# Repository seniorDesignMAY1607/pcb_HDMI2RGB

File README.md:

# pcb_HDMI2RGB
KiCad Design files for HDMI to 24Bit RGB converter used to drive DLP3010 TI EVM board.

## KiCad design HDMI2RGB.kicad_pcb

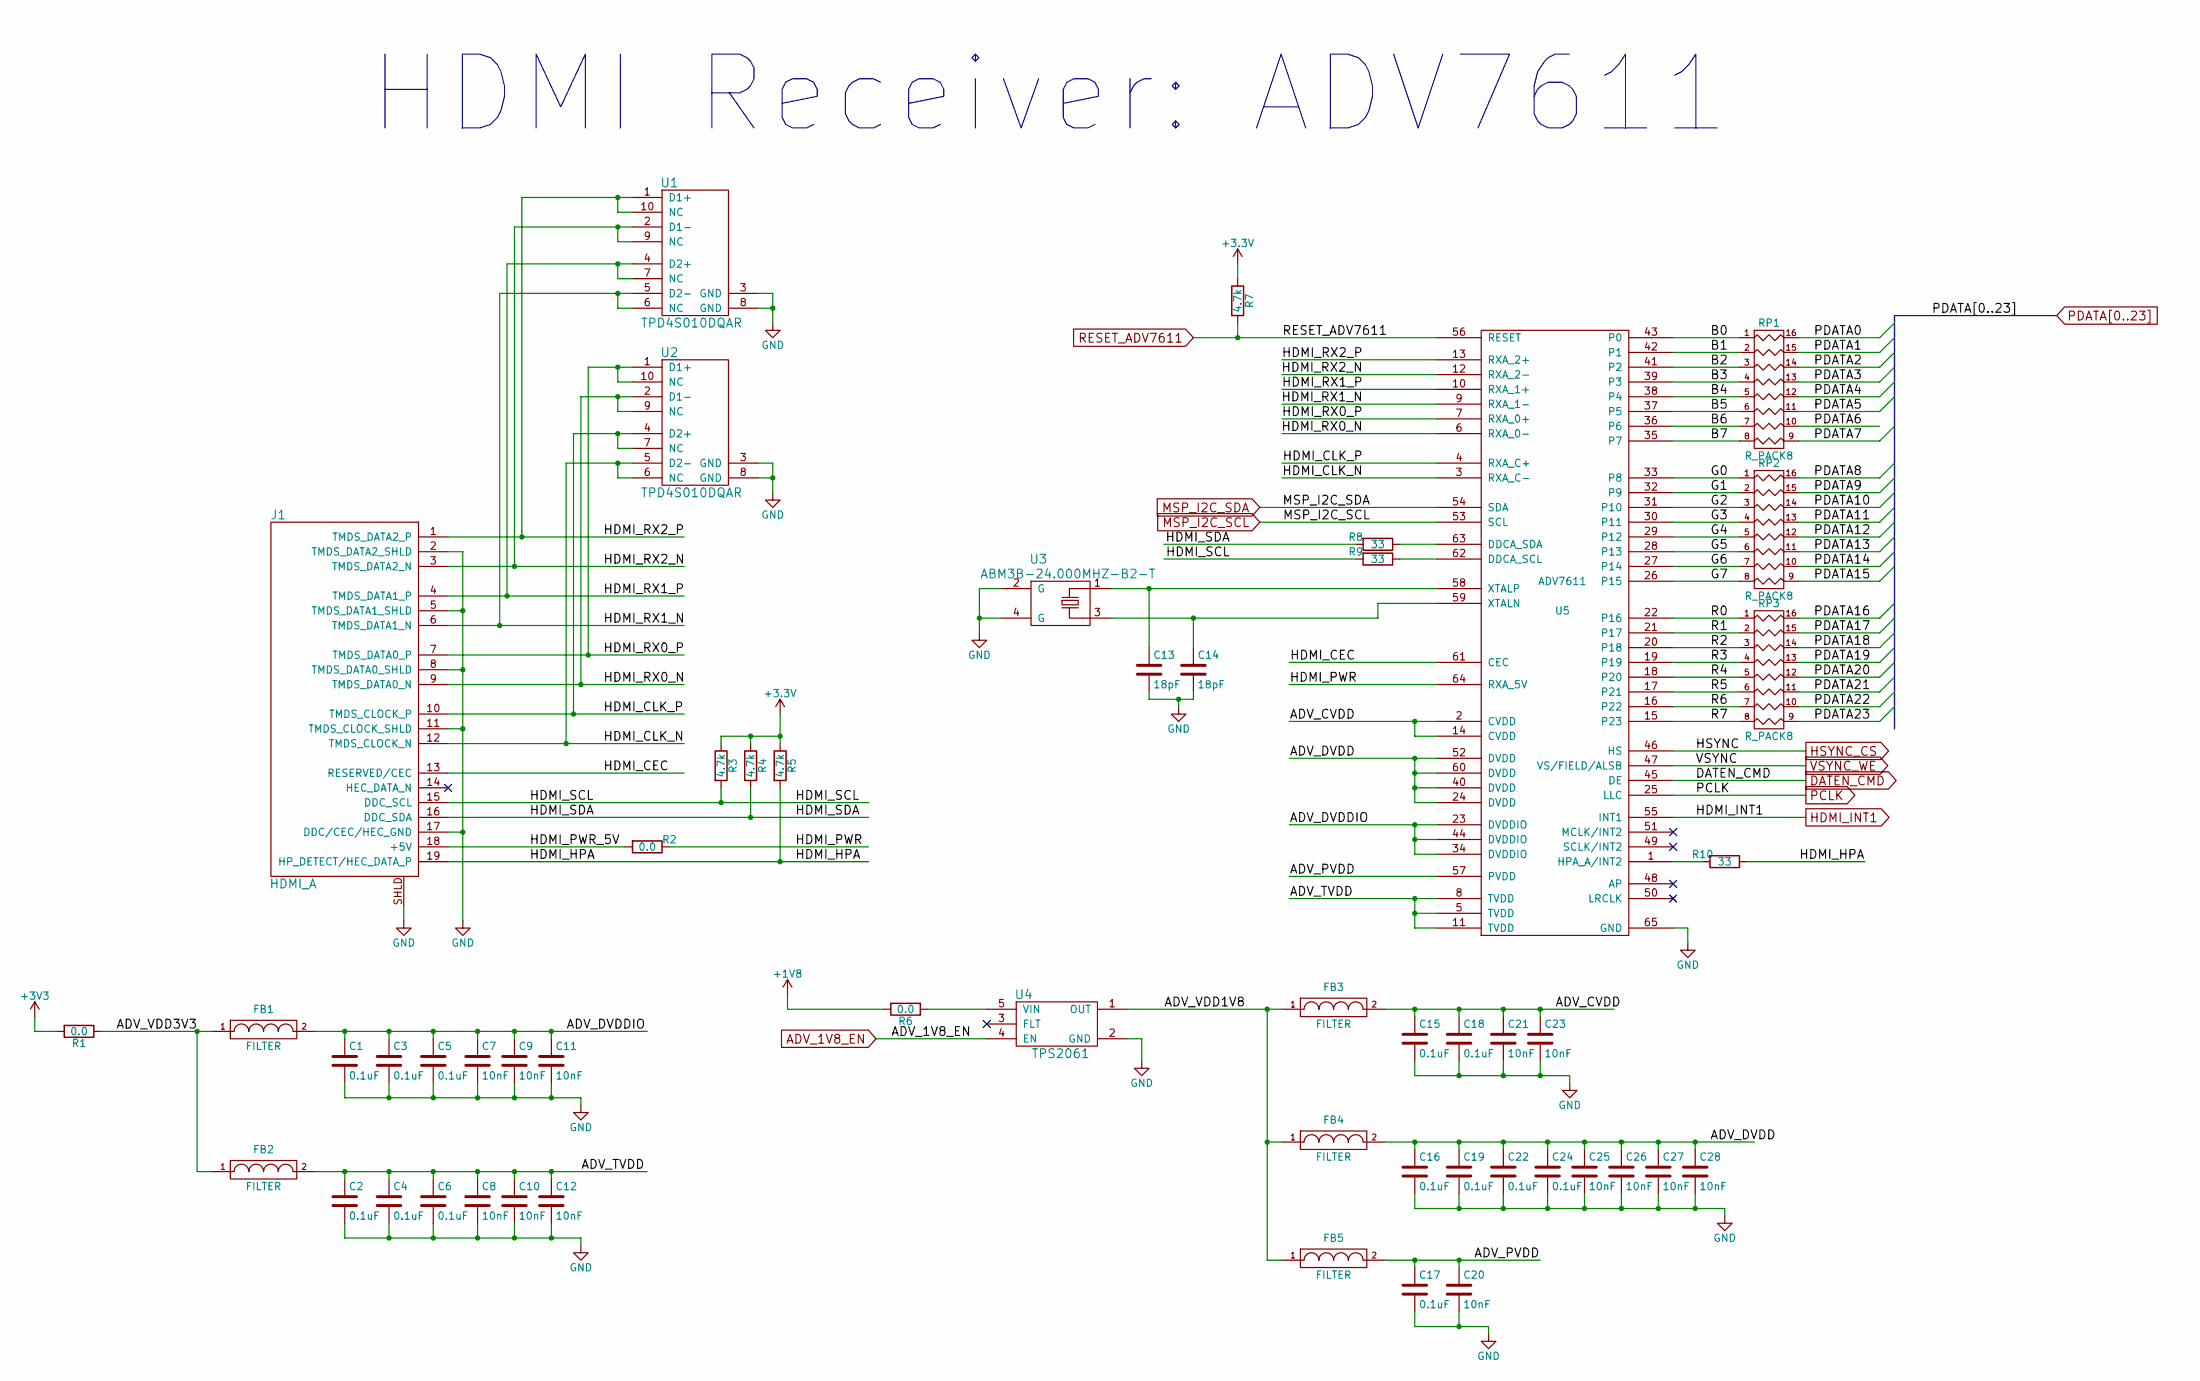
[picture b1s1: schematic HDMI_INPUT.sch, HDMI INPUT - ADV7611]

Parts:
C1, C2, C3, C4, C5, C6, C15, C16, C17, C18, C19, C22, C24: 0.1uF; C_0402; Part # 0402YD104KAT2A
C7, C8, C9, C10, C11, C12, C20, C21, C23, C25, C26, C27, C28: 10nF; C_0402; Part # C0402C103K5RACTU
C13, C14: 18pF; C_0603; Part # 06035A180JAT2A
FB1, FB2, FB3, FB4, FB5: FILTER; C_0603; Part # BLM18AG601SN1D
J1: HDMI_A; FCI_10029449-11[13]RLF
R1, R2, R6: 0.0; R_0402; Part # CRCW06030000Z0EA
R3, R4, R5, R7: 4.7k; R_0402; Part # ERJ-2GEJ472X
R8, R9: 33; R_0402; Part # CRCW040233R0FKED
R10: 33; C_0402; Part # CRCW040233R0FKED
RP1, RP2, RP3: R_PACK8; RPACK-8_0616
U1, U2: TPD4S010DQAR; 10-USON
U3: ABM3B-24.000MHZ-B2-T; XTAL_ABRACON; Part # ABM3B-24.000MHZ-B2-T
U4: TPS2061; SOT-23-5; Part # TPS2061CDBVT
U5: ADV7611; LQFP-64_TH_10x10mm_Pitch0.5mm

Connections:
+1V8: R6.2; also elsewhere on the board
/CONNECTOR/PDATA0: RP1.16 (R1); also elsewhere on the board
/CONNECTOR/PDATA1: RP1.15 (R2); also elsewhere on the board
/CONNECTOR/PDATA2: RP1.14 (R3); also elsewhere on the board
/CONNECTOR/PDATA3: RP1.13 (R4); also elsewhere on the board
/CONNECTOR/PDATA4: RP1.12 (R5); also elsewhere on the board
/CONNECTOR/PDATA5: RP1.11 (R6); also elsewhere on the board
/CONNECTOR/PDATA6: RP1.10 (R7); also elsewhere on the board
/CONNECTOR/PDATA7: RP1.9 (R8); also elsewhere on the board
/CONNECTOR/PDATA8: RP2.16 (R1); also elsewhere on the board
/CONNECTOR/PDATA9: RP2.15 (R2); also elsewhere on the board
/CONNECTOR/PDATA10: RP2.14 (R3); also elsewhere on the board
/CONNECTOR/PDATA11: RP2.13 (R4); also elsewhere on the board
/CONNECTOR/PDATA12: RP2.12 (R5); also elsewhere on the board
/CONNECTOR/PDATA13: RP2.11 (R6); also elsewhere on the board
/CONNECTOR/PDATA14: RP2.10 (R7); also elsewhere on the board
/CONNECTOR/PDATA15: RP2.9 (R8); also elsewhere on the board
/CONNECTOR/PDATA16: RP3.16 (R1); also elsewhere on the board
/CONNECTOR/PDATA17: RP3.15 (R2); also elsewhere on the board
/CONNECTOR/PDATA18: RP3.14 (R3); also elsewhere on the board
/CONNECTOR/PDATA19: RP3.13 (R4); also elsewhere on the board
/CONNECTOR/PDATA20: RP3.12 (R5); also elsewhere on the board
/CONNECTOR/PDATA21: RP3.11 (R6); also elsewhere on the board
/CONNECTOR/PDATA22: RP3.10 (R7); also elsewhere on the board
/CONNECTOR/PDATA23: RP3.9 (R8); also elsewhere on the board
/HDMI_INPUT/ADV_CVDD: C15.1, C18.1, C21.1, C23.1, FB3.2, U5.2 (CVDD), U5.14 (CVDD)
/HDMI_INPUT/ADV_DVDD: C16.1, C19.1, C22.1, C24.1, C25.1, C26.1, C27.1, C28.1, FB4.2, U5.24 (DVDD), U5.40 (DVDD), U5.52 (DVDD), U5.60 (DVDD)
/HDMI_INPUT/ADV_DVDDIO: C1.1, C3.1, C5.1, C7.1, C9.1, C11.1, FB1.2, U5.23 (DVDDIO), U5.34 (DVDDIO), U5.44 (DVDDIO)
/HDMI_INPUT/ADV_PVDD: C17.1, C20.1, FB5.2, U5.57 (PVDD)
/HDMI_INPUT/ADV_TVDD: C2.1, C4.1, C6.1, C8.1, C10.1, C12.1, FB2.2, U5.5 (TVDD), U5.8 (TVDD), U5.11 (TVDD)
/HDMI_INPUT/ADV_VDD1V8: FB3.1, FB4.1, FB5.1, U4.1 (OUT)
/HDMI_INPUT/ADV_VDD3V3: FB1.1, FB2.1, R1.1
/HDMI_INPUT/B0: RP1.1, U5.43 (P0)
/HDMI_INPUT/B1: RP1.2, U5.42 (P1)
/HDMI_INPUT/B2: RP1.3, U5.41 (P2)
/HDMI_INPUT/B3: RP1.4, U5.39 (P3)
/HDMI_INPUT/B4: RP1.5, U5.38 (P4)
/HDMI_INPUT/B5: RP1.6, U5.37 (P5)
/HDMI_INPUT/B6: RP1.7, U5.36 (P6)
/HDMI_INPUT/B7: RP1.8, U5.35 (P7)
/HDMI_INPUT/G0: RP2.1, U5.33 (P8)
/HDMI_INPUT/G1: RP2.2, U5.32 (P9)
/HDMI_INPUT/G2: RP2.3, U5.31 (P10)
/HDMI_INPUT/G3: RP2.4, U5.30 (P11)
/HDMI_INPUT/G4: RP2.5, U5.29 (P12)
/HDMI_INPUT/G5: RP2.6, U5.28 (P13)
/HDMI_INPUT/G6: RP2.7, U5.27 (P14)
/HDMI_INPUT/G7: RP2.8, U5.26 (P15)
/HDMI_INPUT/HDMI_CEC: J1.13 (RESERVED/CEC), U5.61 (CEC)
/HDMI_INPUT/HDMI_CLK_N: J1.12 (TMDS_CLOCK_N), U2.5 (D2-), U2.6 (NC), U5.3 (RXA_C-)
/HDMI_INPUT/HDMI_CLK_P: J1.10 (TMDS_CLOCK_P), U2.4 (D2+), U2.7 (NC), U5.4 (RXA_C+)
/HDMI_INPUT/HDMI_HPA: J1.19 (HP_DETECT/HEC_DATA_P), R5.2, R10.1
/HDMI_INPUT/HDMI_PWR: R2.1, U5.64 (RXA_5V)
/HDMI_INPUT/HDMI_PWR_5V: J1.18 (+5V), R2.2
/HDMI_INPUT/HDMI_RX0_N: J1.9 (TMDS_DATA0_N), U2.2 (D1-), U2.9 (NC), U5.6 (RXA_0-)
/HDMI_INPUT/HDMI_RX0_P: J1.7 (TMDS_DATA0_P), U2.1 (D1+), U2.10 (NC), U5.7 (RXA_0+)
/HDMI_INPUT/HDMI_RX1_N: J1.6 (TMDS_DATA1_N), U1.5 (D2-), U1.6 (NC), U5.9 (RXA_1-)
/HDMI_INPUT/HDMI_RX1_P: J1.4 (TMDS_DATA1_P), U1.4 (D2+), U1.7 (NC), U5.10 (RXA_1+)
/HDMI_INPUT/HDMI_RX2_N: J1.3 (TMDS_DATA2_N), U1.2 (D1-), U1.9 (NC), U5.12 (RXA_2-)
/HDMI_INPUT/HDMI_RX2_P: J1.1 (TMDS_DATA2_P), U1.1 (D1+), U1.10 (NC), U5.13 (RXA_2+)
/HDMI_INPUT/HDMI_SCL: J1.15 (DDC_SCL), R3.2, R9.2
/HDMI_INPUT/HDMI_SDA: J1.16 (DDC_SDA), R4.2, R8.2
/HDMI_INPUT/R0: RP3.1, U5.22 (P16)
/HDMI_INPUT/R1: RP3.2, U5.21 (P17)
/HDMI_INPUT/R2: RP3.3, U5.20 (P18)
/HDMI_INPUT/R3: RP3.4, U5.19
/HDMI_INPUT/R4: RP3.5, U5.18 (P20)
/HDMI_INPUT/R5: RP3.6, U5.17 (P21)
/HDMI_INPUT/R6: RP3.7, U5.16 (P22)
/HDMI_INPUT/R7: RP3.8, U5.15 (P23)
ADV_1V8_EN: U4.4 (EN); also elsewhere on the board
DATEN_CMD: U5.45 (DE); also elsewhere on the board
GND: C1.2, C2.2, C3.2, C4.2, C5.2, C6.2, C7.2, C8.2, C9.2, C10.2, C11.2, C12.2, C13.2, C14.2, C15.2, C16.2, C17.2, C18.2, C19.2, C20.2, C21.2, C22.2, C23.2, C24.2, C25.2, C26.2, C27.2, C28.2, J1.2 (TMDS_DATA2_SHLD), J1.5 (TMDS_DATA1_SHLD), J1.8 (TMDS_DATA0_SHLD), J1.11 (TMDS_CLOCK_SHLD), J1.17 (DDC/CEC/HEC_GND), J1.SHLD, U1.3 (GND), U1.8 (GND), U2.3 (GND), U2.8 (GND), U3.2 (G), U3.4 (G), U4.2 (GND), U5.65 (GND); also elsewhere on the board
HDMI_INT1: U5.55 (INT1); also elsewhere on the board
HSYNC_CS: U5.46 (HS); also elsewhere on the board
MSP_I2C_SCL: U5.53 (SCL); also elsewhere on the board
MSP_I2C_SDA: U5.54 (SDA); also elsewhere on the board
unnamed: C13.1, U3.1, U5.58 (XTALP)
unnamed: C14.1, U3.3, U5.59 (XTALN)
unnamed: R6.1, U4.5 (VIN)
unnamed: R8.1, U5.63 (DDCA_SDA)
unnamed: R9.1, U5.62 (DDCA_SCL)
unnamed: R10.2, U5.1 (HPA_A/INT2)
PCLK: U5.25 (LLC); also elsewhere on the board
RESET_ADV7611: R7.2, U5.56 (RESET); also elsewhere on the board
VSYNC_WE: U5.47 (VS/FIELD/ALSB); also elsewhere on the board

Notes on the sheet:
HDMI Receiver: ADV7611

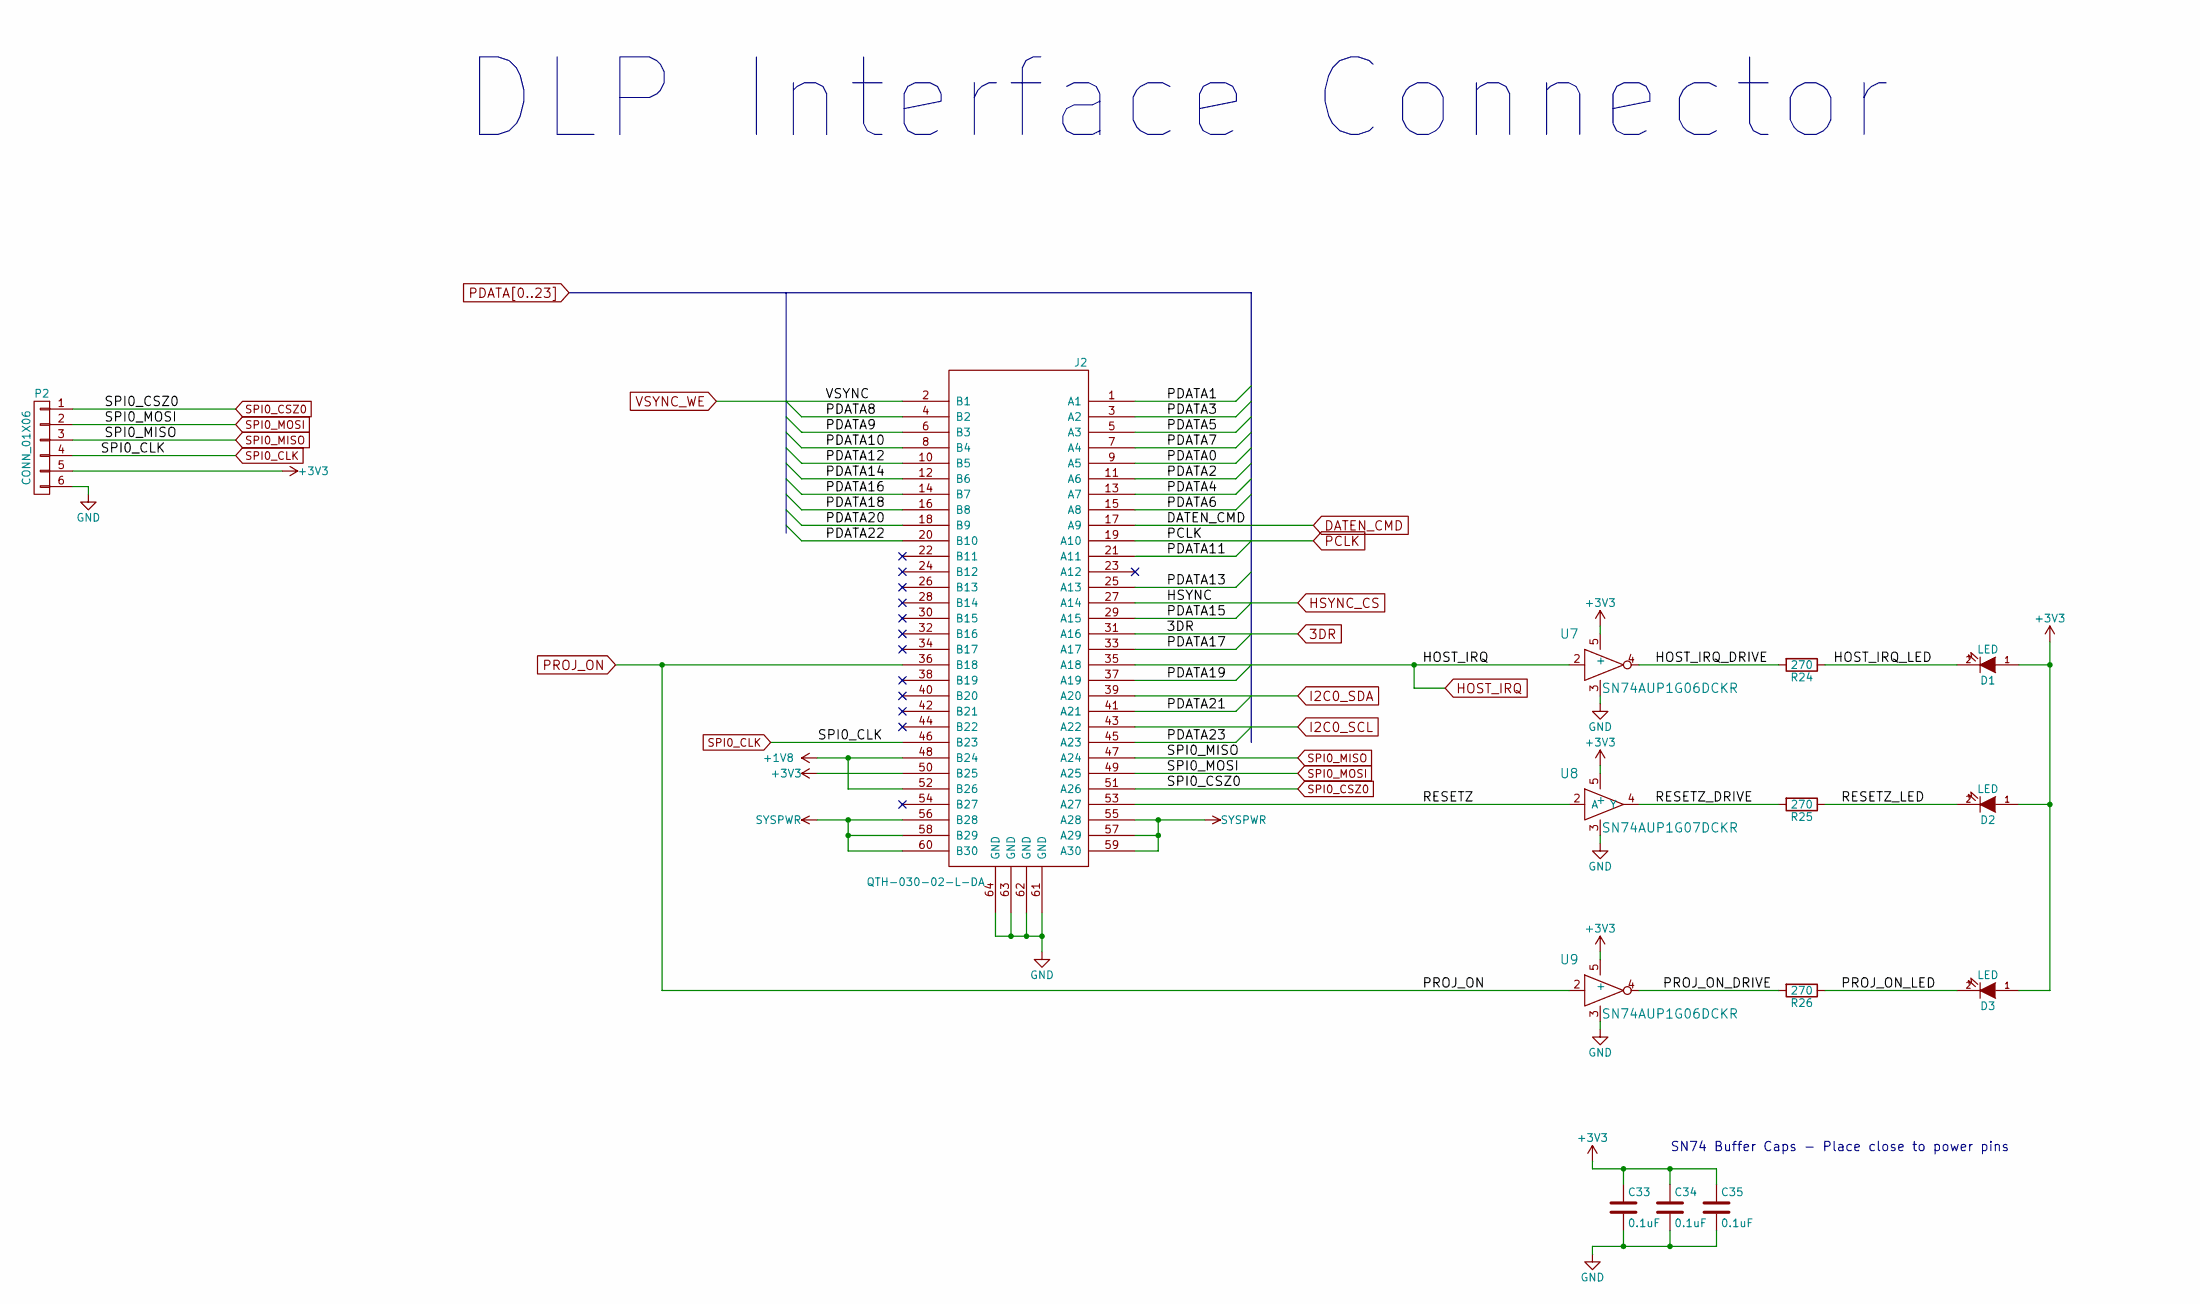
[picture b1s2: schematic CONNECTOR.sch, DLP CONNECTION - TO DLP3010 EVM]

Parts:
C33, C34, C35: 0.1uF; C_0402; Part # 0402YD104KAT2A
D1, D2, D3: LED; C_0603; Part # LTST-C190KGKT
J2: QTH-030-02-L-DA; QTH-030-02-L-D-A; Part # QTH-030-L-D-A
P2: CONN_01X06; Pin_Header_Straight_1x06
R24, R25, R26: 270; R_0402; Part # CRCW0402270RFKED
U7, U9: SN74AUP1G06DCKR; SC-70-5; Part # SN74AUP1G06DCKR
U8: SN74AUP1G07DCKR; SC-70-5; Part # SN74AUP1G07DCKR

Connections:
3DR: J2.31 (A16)
+1V8: J2.48 (B24), J2.52 (B26); also elsewhere on the board
/CONNECTOR/HOST_IRQ_DRIVE: R24.2, U7.4
/CONNECTOR/HOST_IRQ_LED: D1.2 (K), R24.1
/CONNECTOR/PDATA0: J2.9 (A5); also elsewhere on the board
/CONNECTOR/PDATA1: J2.1 (A1); also elsewhere on the board
/CONNECTOR/PDATA2: J2.11 (A6); also elsewhere on the board
/CONNECTOR/PDATA3: J2.3 (A2); also elsewhere on the board
/CONNECTOR/PDATA4: J2.13 (A7); also elsewhere on the board
/CONNECTOR/PDATA5: J2.5 (A3); also elsewhere on the board
/CONNECTOR/PDATA6: J2.15 (A8); also elsewhere on the board
/CONNECTOR/PDATA7: J2.7 (A4); also elsewhere on the board
/CONNECTOR/PDATA8: J2.4 (B2); also elsewhere on the board
/CONNECTOR/PDATA9: J2.6 (B3); also elsewhere on the board
/CONNECTOR/PDATA10: J2.8 (B4); also elsewhere on the board
/CONNECTOR/PDATA11: J2.21 (A11); also elsewhere on the board
/CONNECTOR/PDATA12: J2.10 (B5); also elsewhere on the board
/CONNECTOR/PDATA13: J2.25 (A13); also elsewhere on the board
/CONNECTOR/PDATA14: J2.12 (B6); also elsewhere on the board
/CONNECTOR/PDATA15: J2.29 (A15); also elsewhere on the board
/CONNECTOR/PDATA16: J2.14 (B7); also elsewhere on the board
/CONNECTOR/PDATA17: J2.33 (A17); also elsewhere on the board
/CONNECTOR/PDATA18: J2.16 (B8); also elsewhere on the board
/CONNECTOR/PDATA19: J2.37 (A19); also elsewhere on the board
/CONNECTOR/PDATA20: J2.18 (B9); also elsewhere on the board
/CONNECTOR/PDATA21: J2.41 (A21); also elsewhere on the board
/CONNECTOR/PDATA22: J2.20 (B10); also elsewhere on the board
/CONNECTOR/PDATA23: J2.45 (A23); also elsewhere on the board
/CONNECTOR/PROJ_ON_DRIVE: R26.2, U9.4
/CONNECTOR/PROJ_ON_LED: D3.2 (K), R26.1
/CONNECTOR/RESETZ: J2.53 (A27), U8.2 (A)
/CONNECTOR/RESETZ_DRIVE: R25.2, U8.4 (Y)
/CONNECTOR/RESETZ_LED: D2.2 (K), R25.1
DATEN_CMD: J2.17 (A9); also elsewhere on the board
GND: C33.2, C34.2, C35.2, J2.61 (GND), J2.62 (GND), J2.63 (GND), J2.64 (GND), P2.6, U7.3, U8.3, U9.3; also elsewhere on the board
HOST_IRQ: J2.35 (A18), U7.2; also elsewhere on the board
HSYNC_CS: J2.27 (A14); also elsewhere on the board
I2C0_SCL: J2.43 (A22)
I2C0_SDA: J2.39 (A20)
PCLK: J2.19 (A10); also elsewhere on the board
PROJ_ON: J2.36 (B18), U9.2; also elsewhere on the board
SPI0_CLK: J2.46 (B23), P2.4
SPI0_CSZ0: J2.51 (A26), P2.1
SPI0_MISO: J2.47 (A24), P2.3
SPI0_MOSI: J2.49 (A25), P2.2
SYSPWR: J2.55 (A28), J2.56 (B28), J2.57 (A29), J2.58 (B29), J2.59 (A30), J2.60 (B30); also elsewhere on the board
VSYNC_WE: J2.2 (B1); also elsewhere on the board

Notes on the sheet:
SN74 Buffer Caps - Place close to power pins
DLP Interface Connector

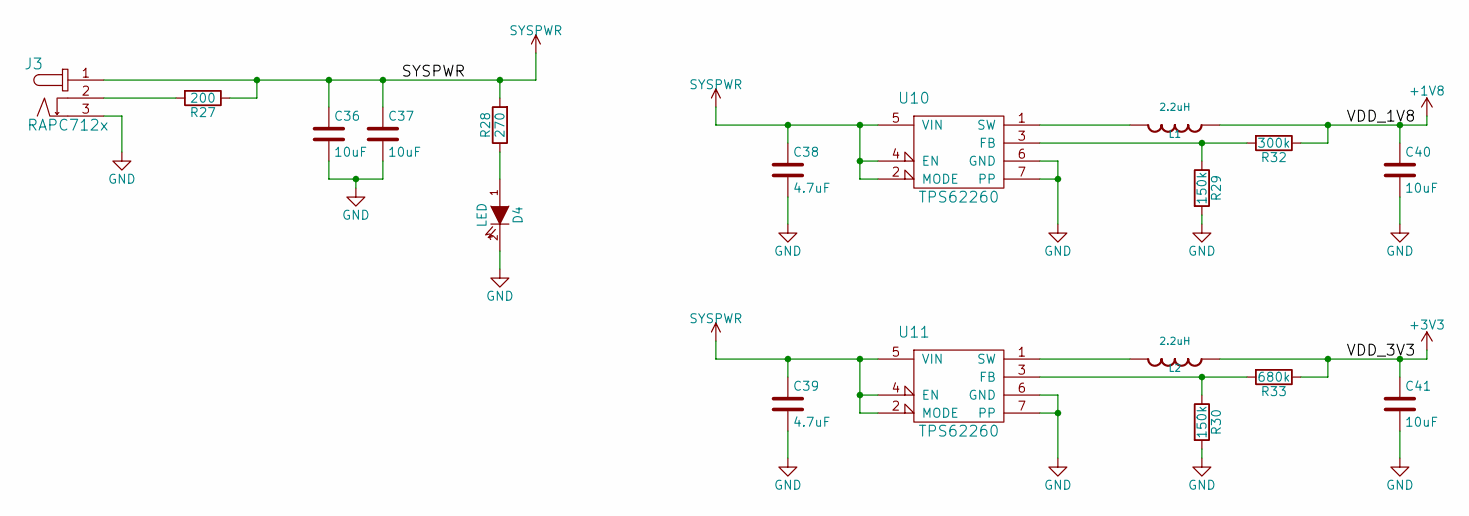
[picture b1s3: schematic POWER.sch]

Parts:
C36, C37, C40, C41: 10uF; C_0805; Part # C0805C106K4PACTU
C38, C39: 4.7uF; C_0805; Part # C0805C475K8PACTU
D4: LED; C_0603; Part # LTST-C190KGKT
J3: RAPC712x; RAPC712; Part # RAPC712X
L1, L2: 2.2uH; C_1206; Part # LQM31PN2R2M00L
R27: 200; R_0805; Part # CRCW0805200RFKEA
R28: 270; R_0603; Part # CRCW0402270RFKED
R29, R30: 150k; R_0603; Part # CRCW0402150KFKED
R32: 300k; R_0603; Part # ERJ-2RKF3003X
R33: 680k; R_0603; Part # ERJ-2GEJ684X
U10, U11: TPS62260; WSON-6; Part # TPS62260DRVT

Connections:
+1V8: C40.1, L1.2, R32.1; also elsewhere on the board
GND: C36.2, C37.2, C38.2, C39.2, C40.2, C41.2, D4.2 (K), J3.3, R29.2, R30.2, U10.6 (GND), U10.7 (PP), U11.6 (GND), U11.7 (PP); also elsewhere on the board
unnamed: D4.1 (A), R28.1
unnamed: J3.2, R27.2
unnamed: L1.1, U10.1 (SW)
unnamed: L2.1, U11.1 (SW)
unnamed: R29.1, R32.2, U10.3 (FB)
unnamed: R30.1, R33.2, U11.3 (FB)
SYSPWR: C36.1, C37.1, C38.1, C39.1, J3.1, R27.1, R28.2, U10.2 (MODE), U10.4 (EN), U10.5 (VIN), U11.2 (MODE), U11.4 (EN), U11.5 (VIN); also elsewhere on the board

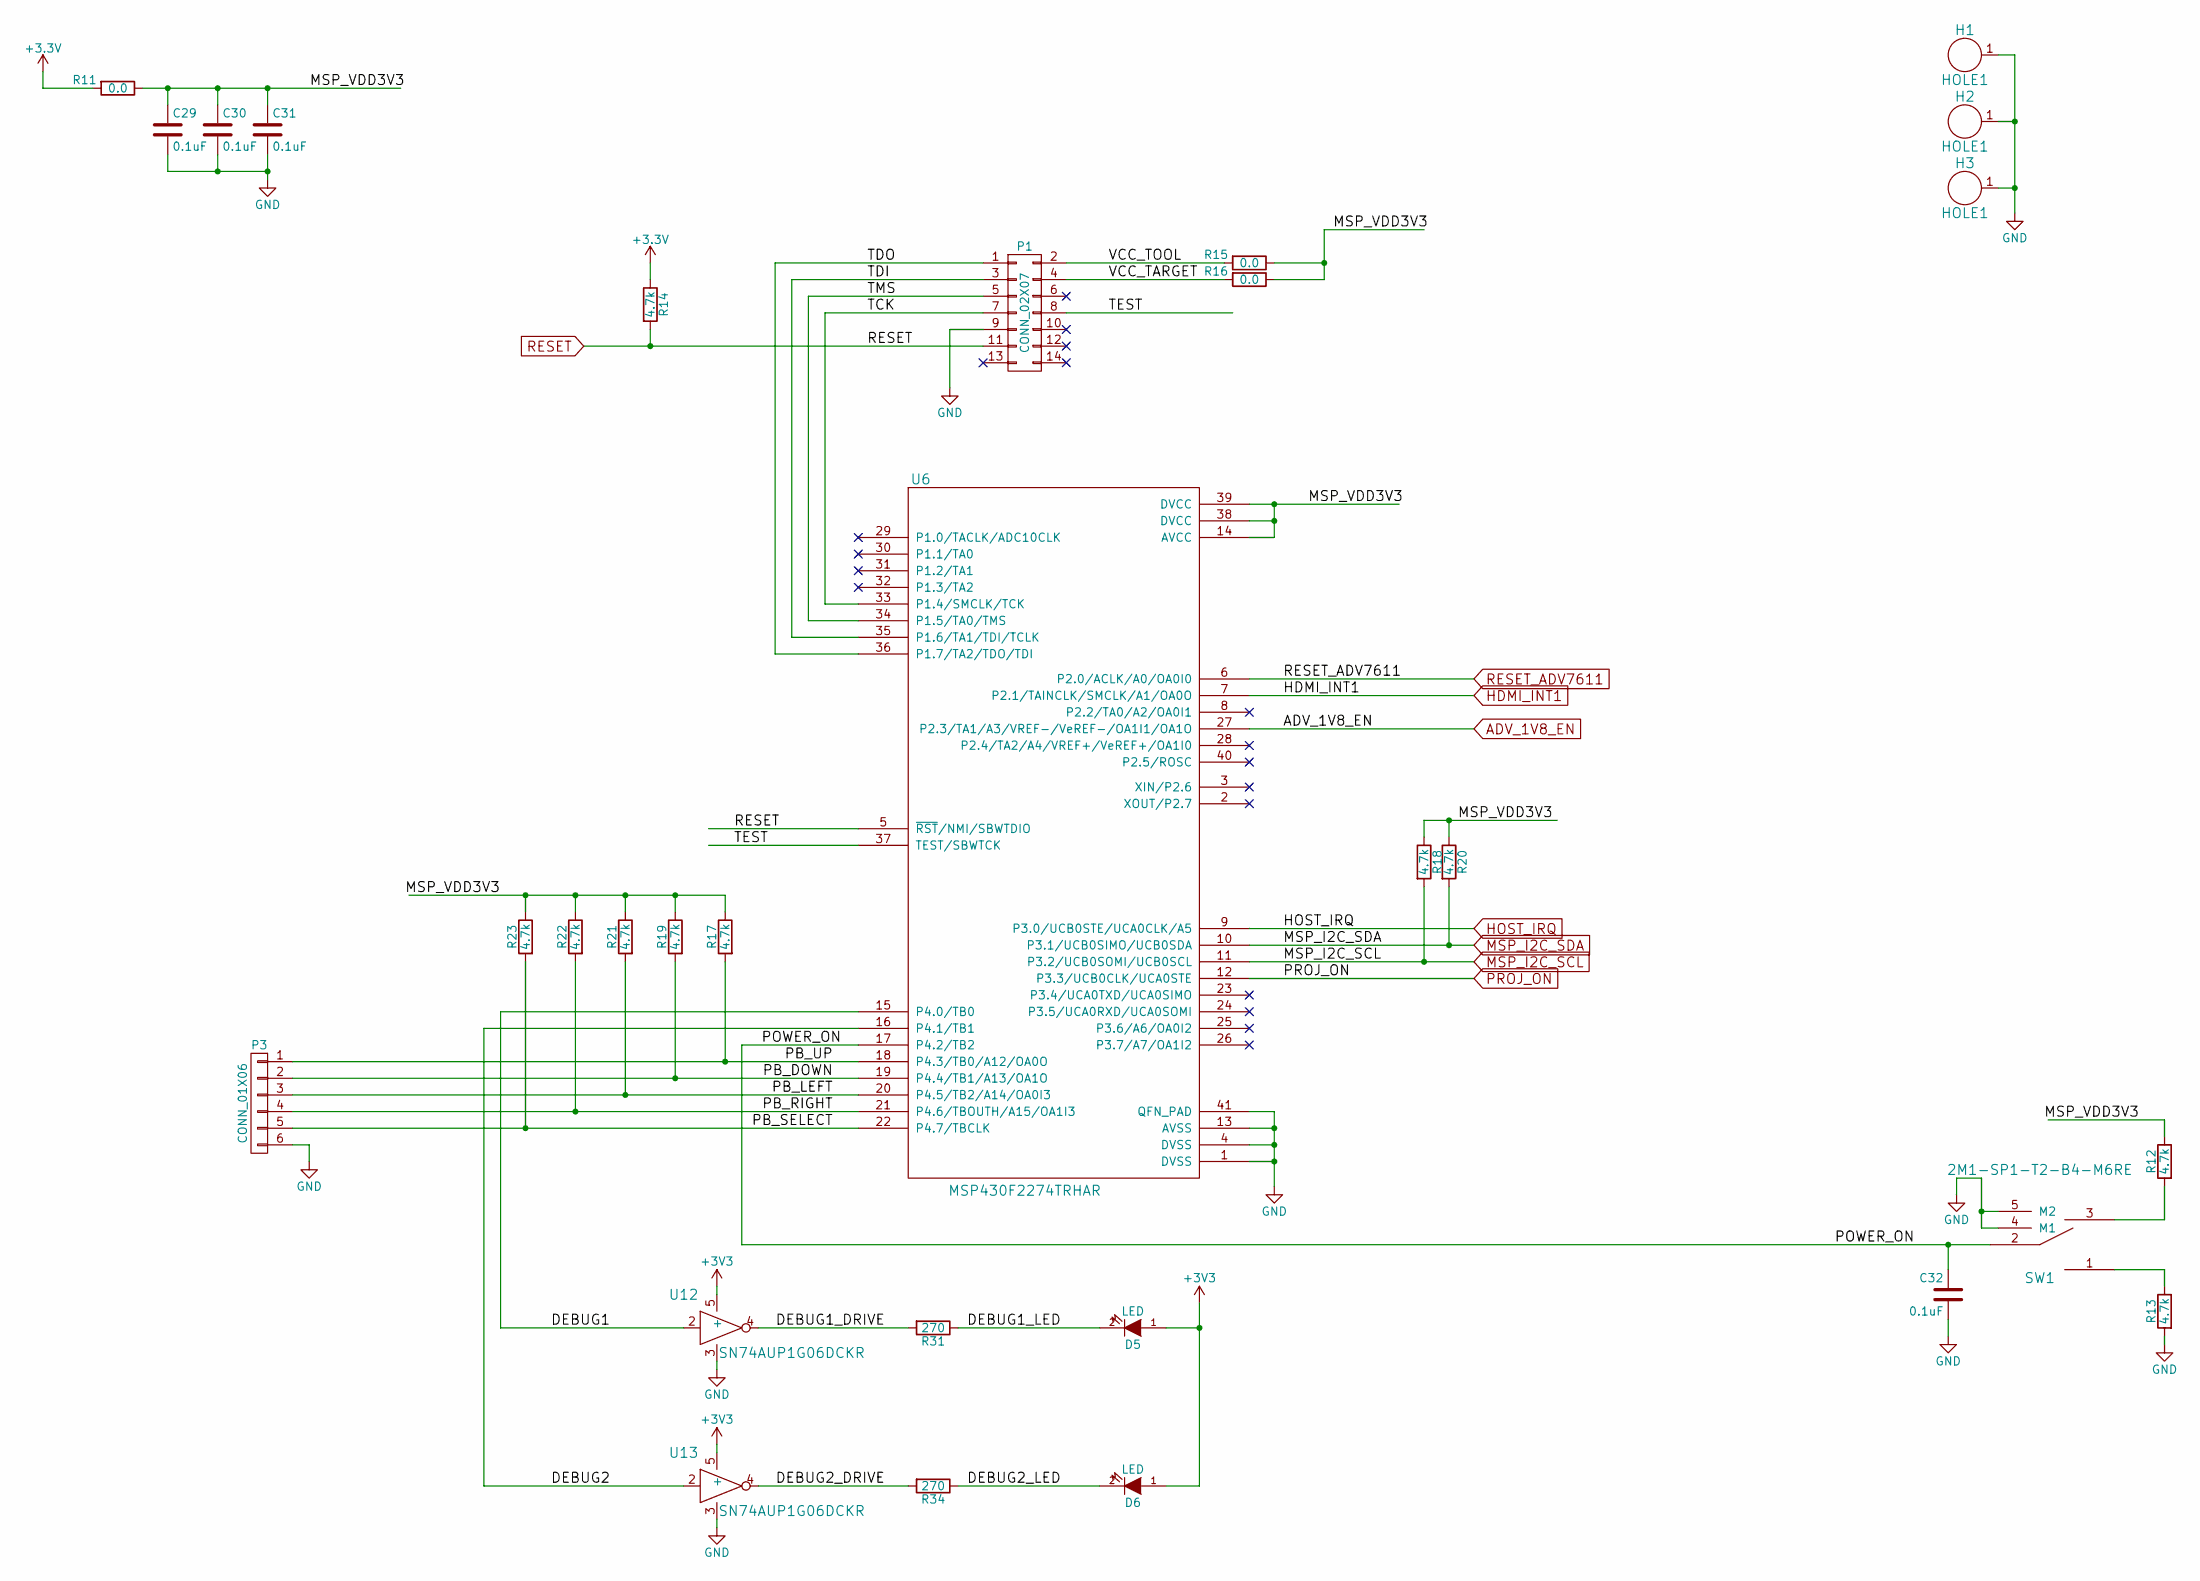
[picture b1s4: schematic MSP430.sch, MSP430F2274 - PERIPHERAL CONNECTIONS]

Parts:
C29, C30, C31, C32: 0.1uF; C_0402; Part # 0402YD104KAT2A
D5, D6: LED; C_0603; Part # LTST-C190KGKT
H1, H2, H3: HOLE1; MountingHole_4.3mm_M4_Pad
P1: CONN_02X07; IDC_Header_Straight_14pins
P3: CONN_01X06; Pin_Header_Straight_1x06
R11, R15, R16: 0.0; R_0402; Part # CRCW06030000Z0EA
R12, R13, R14, R17, R18, R19, R20, R21, R22, R23: 4.7k; R_0402; Part # ERJ-2GEJ472X
R31, R34: 270; R_0402; Part # CRCW0402270RFKED
SW1: 2M1-SP1-T2-B4-M6RE; Part # 2M1-SP1-T2-B4-M6RE
U6: MSP430F2274TRHAR; QFN-40-1EP_6x6mm_Pitch0.5mm
U12, U13: SN74AUP1G06DCKR; SC-70-5; Part # SN74AUP1G06DCKR

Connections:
/MSP430/DEBUG1: U6.15 (P4.0/TB0), U12.2
/MSP430/DEBUG1_DRIVE: R31.2, U12.4
/MSP430/DEBUG1_LED: D5.2 (K), R31.1
/MSP430/DEBUG2: U6.16 (P4.1/TB1), U13.2
/MSP430/DEBUG2_DRIVE: R34.2, U13.4
/MSP430/DEBUG2_LED: D6.2 (K), R34.1
/MSP430/MSP_VDD3V3: C29.1, C30.1, C31.1, R11.1, R12.1, R15.1, R16.1, R17.1, R18.1, R19.1, R20.1, R21.1, R22.1, R23.1, U6.14 (AVCC), U6.38 (DVCC), U6.39 (DVCC)
/MSP430/PB_DOWN: P3.2, R19.2, U6.19 (P4.4/TB1/A13/OA1O)
/MSP430/PB_LEFT: P3.3, R21.2, U6.20 (P4.5/TB2/A14/OA0I3)
/MSP430/PB_RIGHT: P3.4, R22.2, U6.21 (P4.6/TBOUTH/A15/OA1I3)
/MSP430/PB_SELECT: P3.5, R23.2, U6.22 (P4.7/TBCLK)
/MSP430/PB_UP: P3.1, R17.2, U6.18 (P4.3/TB0/A12/OA0O)
/MSP430/POWER_ON: C32.1, SW1.2, U6.17 (P4.2/TB2)
/MSP430/TCK: P1.7, U6.33 (P1.4/SMCLK/TCK)
/MSP430/TDI: P1.3, U6.35 (P1.6/TA1/TDI/TCLK)
/MSP430/TDO: P1.1, U6.36 (P1.7/TA2/TDO/TDI)
/MSP430/TEST: P1.8, U6.37 (TEST/SBWTCK)
/MSP430/TMS: P1.5, U6.34 (P1.5/TA0/TMS)
/MSP430/VCC_TARGET: P1.4, R16.2
/MSP430/VCC_TOOL: P1.2, R15.2
ADV_1V8_EN: U6.27 (P2.3/TA1/A3/VREF-/VeREF-/OA1I1/OA1O); also elsewhere on the board
GND: C29.2, C30.2, C31.2, C32.2, H1.1, H2.1, H3.1, P1.9, P3.6, R13.2, SW1.4 (M1), SW1.5 (M2), U6.1 (DVSS), U6.4 (DVSS), U6.13 (AVSS), U6.41 (QFN_PAD), U12.3, U13.3; also elsewhere on the board
HDMI_INT1: U6.7 (P2.1/TAINCLK/SMCLK/A1/OA0O); also elsewhere on the board
HOST_IRQ: U6.9 (P3.0/UCB0STE/UCA0CLK/A5); also elsewhere on the board
MSP_I2C_SCL: R18.2, U6.11 (P3.2/UCB0SOMI/UCB0SCL); also elsewhere on the board
MSP_I2C_SDA: R20.2, U6.10 (P3.1/UCB0SIMO/UCB0SDA); also elsewhere on the board
unnamed: R12.2, SW1.3
unnamed: R13.1, SW1.1
PROJ_ON: U6.12 (P3.3/UCB0CLK/UCA0STE); also elsewhere on the board
RESET: P1.11, R14.2, U6.5 (~RST~/NMI/SBWTDIO)
RESET_ADV7611: U6.6 (P2.0/ACLK/A0/OA0I0); also elsewhere on the board

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
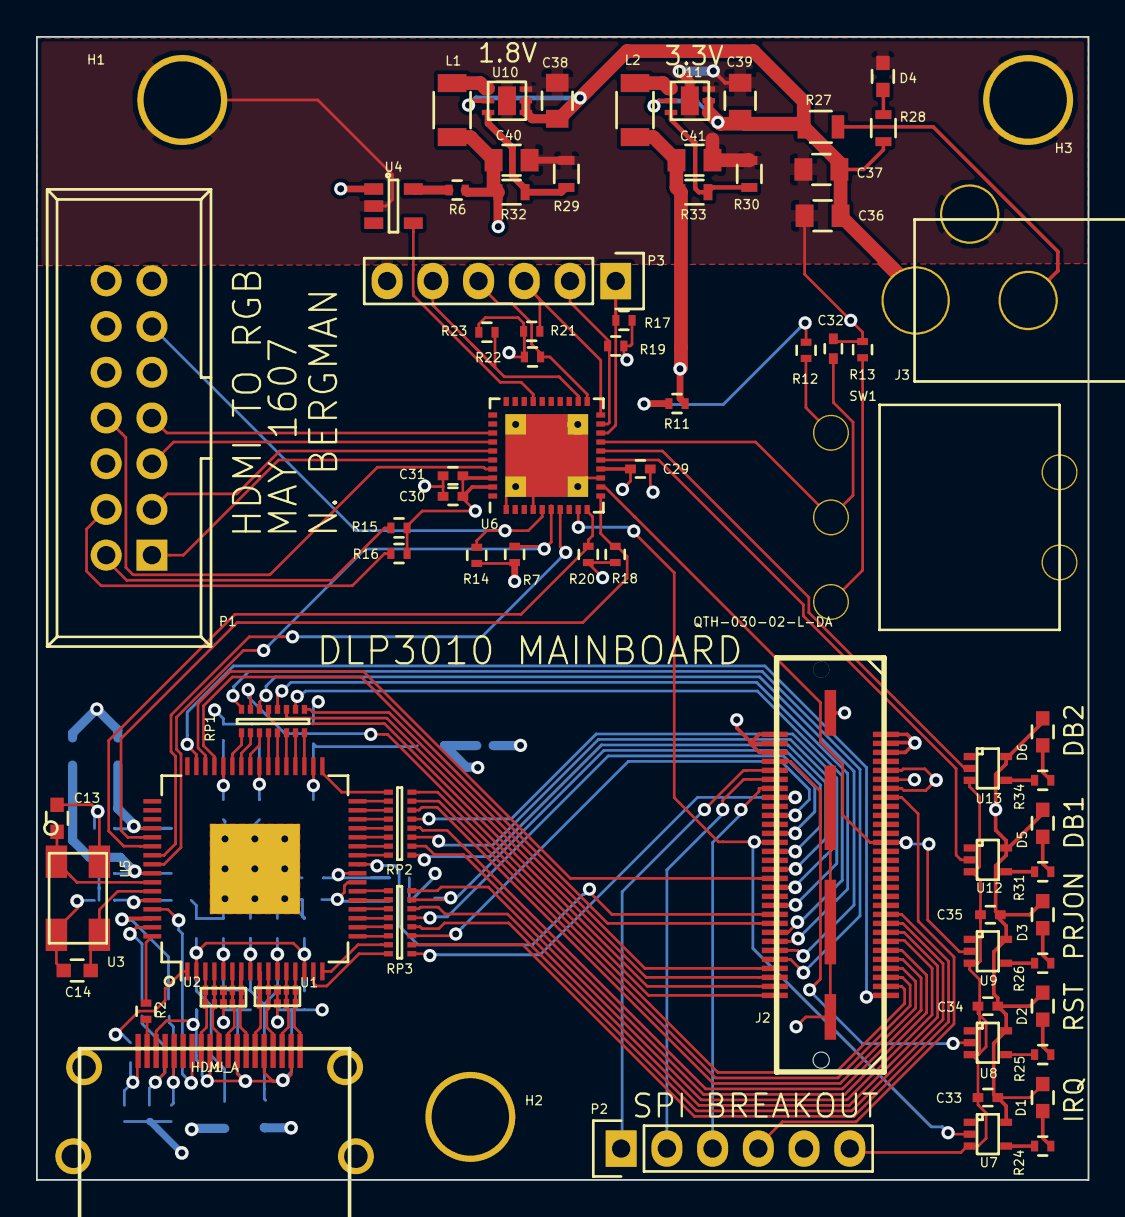
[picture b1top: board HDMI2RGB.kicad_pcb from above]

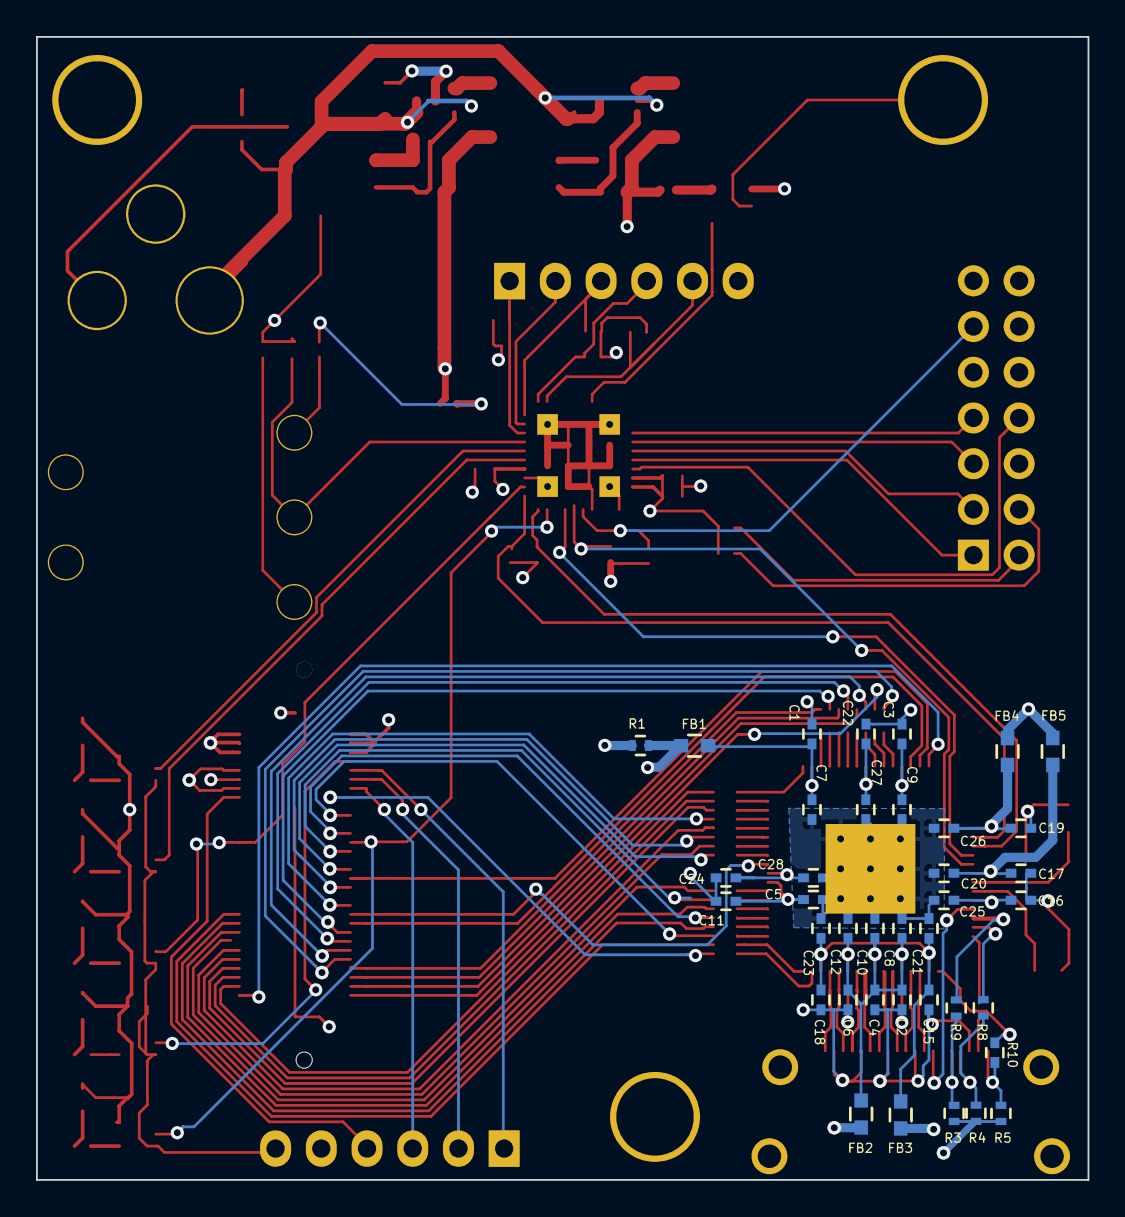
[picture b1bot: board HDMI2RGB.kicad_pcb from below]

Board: 4 copper layers, 58.4 x 63.5 mm, 114 parts (38 on the bottom side), 130 nets.

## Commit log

2016-03-27 Created KiCad project
2016-03-27 HDMI is almost routed, added connector
2016-03-27 Added pdata lines and ran bus connections
2016-03-27 Started PCB Layout, added mounting holes, connectors, in correct locations
2016-03-28 Hdmi and RGB is routed, waiting for trace matching
2016-03-30 ADV7611 power caps are placed and routed
2016-03-30 Basic layout of all components on PCB
2016-03-30 Routing power, changed buttons connections, and a few pther connections
2016-03-31 First Final -- Waiting for Checker
2016-03-31 Schematic PDF
2016-03-31 Schematic Titles
2016-03-31 Adjusted all RefDes
2016-03-31 New Schematic PDF
2016-03-31 Added silkscreen labels and title to PCB
2016-03-31 Changed via size to 23mil diameter
2016-03-31 Added BOM
2016-04-01 Changed BOM for several components
2016-04-01 Added Logo
2016-04-07 New Schematic PDF and BOM
2016-04-07 Re-Plotted Schematic
